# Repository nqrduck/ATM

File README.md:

# ATM (Automatic Tuning and Matching) System

## Automated Tuning and Matching

Tuning and Matching of the resonator coil is an essential part of Nuclear Quadrupole Resonance (NQR) spectroscopy. Because unknown samples are often scanned over large frequency ranges, Tuning and Matching has to be performed frequently. For high Q probe coils using mechanically trimmable capacitors, this is a long and tedious task.
To overcome this issue, an automatic Tuning and Matching system was developed using widely available low-cost components. Stepper drivers control mechanically trimmable capacitors and a microcontroller measures the Return Loss at resonance frequency. The system is capable of Tuning and Matching of a resonator coil in a frequency range from 75 to 125 MHz. It can also measure the Return Loss of the probe coil at its resonance frequency.

Additionally the system is capable of Tuning and Matching of NQR probe coils using varactor diodes. In this case the system can output a Tuning and Matching voltage in a range from 0 to 5V. 

This system is best used in combination with the [NQRduck](https://git.private.coffee/nqrduck) project which provides a graphical user interface for the ATM-system. Specifically, the [nqrduck-autotm](https://git.private.coffee/nqrduck/nqrduck-autotm) module is used to control the ATM-system.

The C++ program is then running on the ESP32 microcontroller. The NQRduck autotm module communicates with the ESP32 microcontroller using the USB interface.

## Features
- Homing of the probe coil steppers using the sensorless load detection of TMC2130 stepper drivers. 
- A mechanically tunable probe coil can be tuned and matched in the frequency range of 75-125MHz.
- $S_{11}$ measurements can be performed at a frequency with a fixed position for the tuning and matching capacitors.
- Electrically tunable probe coils can be tuned and matched in the frequency range of 75-125MHz. 

## System overview
The ATM-system consists of multiple separate hardware components and multiple signal paths. One signal path is used to measure the reflection (characterized by the Return Loss) at a frequency with a fixed position for the tuning and matching capacitors. It is structured as following:

1.  A frequency synthesizer (ADF4351) outputs an RF signal to a filterbank. 
2. The filterbank filters out harmonic components of the frequency synthesizer's output.
3. The filtered signal is guided to a directional coupler setup. The directional coupler is connected to the resonator circuit and decouples the forward signal and the signal reflected at the resonator circuit. 
4. The forward and reflected signals are converted to a DC signal us an AD8302.
5. An ADC reads in the output of the AD8302 and calculates the Return Loss.

Since the system also needs to be able to adjust the mechanically trimmable capacitors, stepper motors have to be controlled.

1. A microcontroller sends commands to two stepper drivers using a Serial Peripheral Interface (SPI).
2. Those stepper drivers control the steppers which are mechanically coupled to the the tuning and matching capacitors of the probe coil.  

For electrically tunable probe coils the ESP32 uses the ADAC click to output a voltage to the varactor diodes.

## Hardware
Schematics for the electrical circuit and mechanical housing will be added soon. 

## Install instructions
1. Download the project as a zip file and import it as a platformio project. 
2. Connect your ESP32 microcontroller to your PC and flash the firmware onto it. 

For the installation of the NQRduck autoTM module please refer to the [NQRduck](https://git.private.coffee/nqrduck) documentation.

# Commands
The user can input different commands to the ATM-system using the serial interface of the ESP32. The general structure of such a command is a single character followed by a float value. The float value is only needed for certain commands.

# Results
A mechanically tunable probe coil was tuned and from 83MHz to 87MHz with a step size of 0.1MHz. The resulting reflection coefficient was then measured using the VNA (ZVL3, Rohde & Schwarz, Munich, Germany). The measured values were plotted using Matplotlib.

For the electrically tunable probe coil the probe coil was tuned and matched from 83 to 84MHz with a step size of 0.1MHz. The resulting reflection coefficient was then measured using the VNA (ZVL3, Rohde & Schwarz, Munich, Germany). The measured values were plotted using Matplotlib.

## Future work
- Optimization for $S_{11}$ measurements. Right now the maximum achievable matching is about -25dB.
- Improve the calibration for $S_{11}$ measurements. Right now the setup is very impractical. 

## References
- [adf4351](https://github.com/dfannin/adf4351) by David Fannin was modified to be used with an ESP32 microcontroller. 
- [TMC2130Stepper](https://github.com/teemuatlut/TMC2130Stepper) by teemuatlut was used for the TMC2130 Stepper drivers.
- [AD5593R](https://github.com/LukasJanavicius/AD5593R-Arduino-ESP32-Library) by LukasJanavicius was used for the AD5593R ADC.
- [ArduiTaM](https://doi.org/10.5194/mr-1-105-2020) by Jouda et al. was an inspiration for the implementation.

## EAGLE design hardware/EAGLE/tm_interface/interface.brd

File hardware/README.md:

# Notes
These files are out of date and are not used in the current version of the ATM. I will update this documentation soon (hopefully).

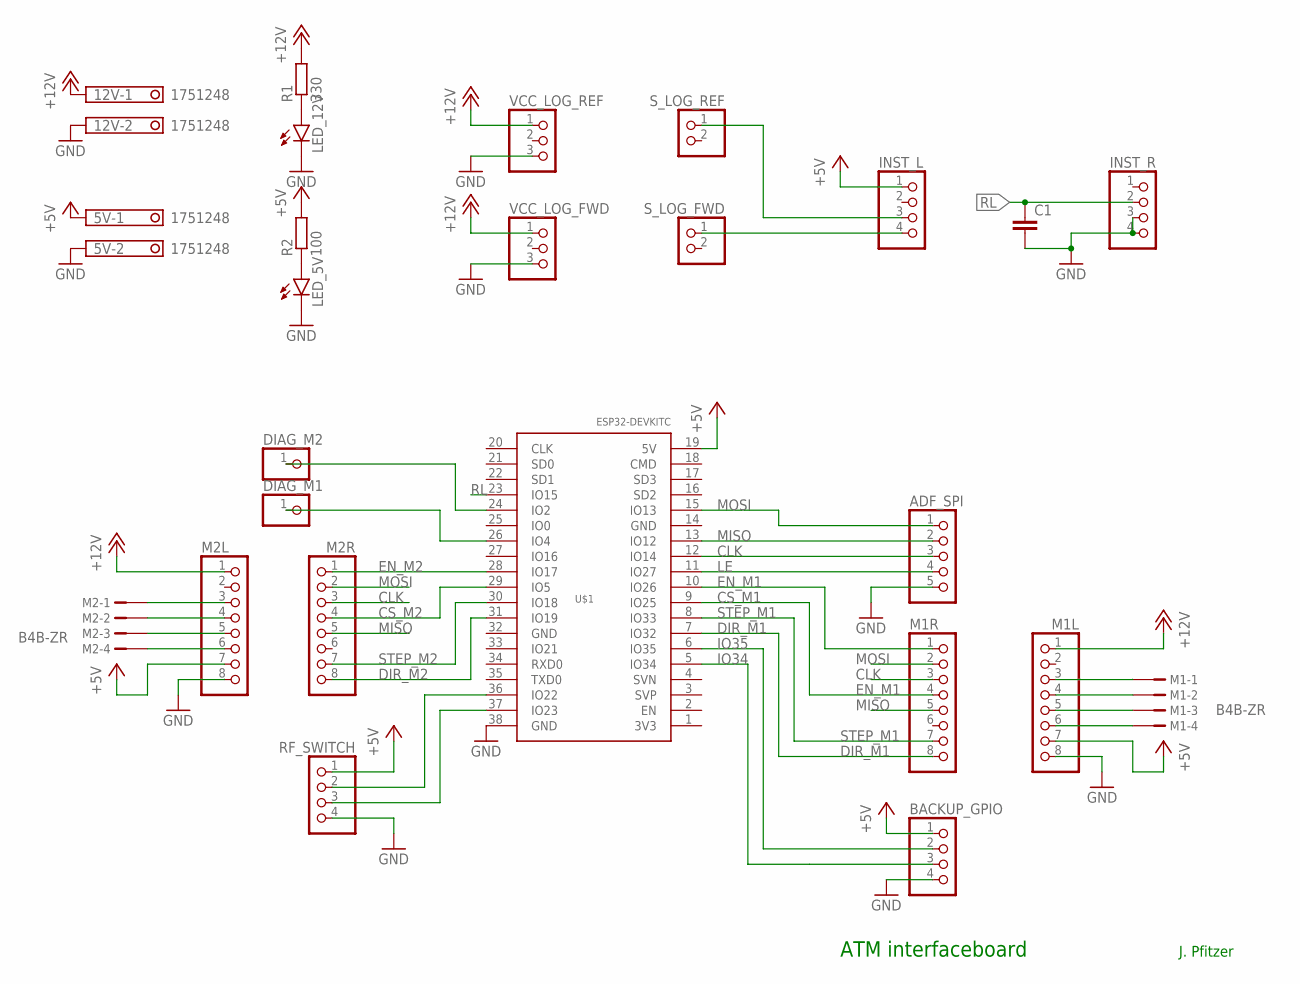
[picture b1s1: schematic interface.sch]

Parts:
5V, 12V: 1751248
ADF_SPI: PINHD-1X5; 1X05
BACKUP_GPIO: PINHD-1X4; 1X04
C1: C-EU025-025X050; C025-025X050
DIAG_M1, DIAG_M2: PINHD-1X1; 1X01
INST_L: PINHD-1X4; 1X04
INST_R: PINHD-1X4; 1X04
LED_5V, LED_12V: LED5MM
M1, M2: B4B-ZR
M1L, M1R, M2L, M2R: PINHD-1X8; 1X08
R1: 330; 0207/12
R2: 100; 0207/12
RF_SWITCH: PINHD-1X4; 1X04
S_LOG_FWD: PINHD-1X2; 1X02
S_LOG_REF: PINHD-1X2; 1X02
U$1: ESP32DEVKITC; ESP32-DEVKITC
VCC_LOG_FWD: PINHD-1X3; 1X03
VCC_LOG_REF: PINHD-1X3; 1X03

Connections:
+5V: 5V.1, BACKUP_GPIO.1, INST_L.1, M1L.7, M2L.7, R2.2, RF_SWITCH.1, U$1.19 (5V)
+12V: 12V.1, M1L.1, M2L.1, R1.2, VCC_LOG_FWD.1, VCC_LOG_REF.1
CLK: ADF_SPI.3, M1R.3, M2R.3, U$1.12 (IO14)
CS_M1: M1R.4, U$1.9 (IO25)
CS_M2: M2R.4, U$1.29 (IO5)
DIR_M1: M1R.8, U$1.7 (IO32)
DIR_M2: M2R.8, U$1.31 (IO19)
EN_M1: M1R.1, U$1.10 (IO26)
EN_M2: M2R.1, U$1.28 (IO17)
GND: 5V.2, 12V.2, ADF_SPI.5, BACKUP_GPIO.4, C1.2, INST_R.3, INST_R.4, LED_5V.K (C), LED_12V.K (C), M1L.8, M2L.8, RF_SWITCH.4, U$1.38 (GND), VCC_LOG_FWD.3, VCC_LOG_REF.3
IO34: BACKUP_GPIO.3, U$1.5 (IO34)
IO35: BACKUP_GPIO.2, U$1.6 (IO35)
LE: ADF_SPI.4, U$1.11 (IO27)
MISO: ADF_SPI.2, M1R.5, M2R.5, U$1.13 (IO12)
MOSI: ADF_SPI.1, M1R.2, M2R.2, U$1.15 (IO13)
unnamed: M1.1, M1L.3
unnamed: M1.2, M1L.4
unnamed: M1.3, M1L.5
unnamed: M1.4, M1L.6
unnamed: M2.1, M2L.3
unnamed: M2.2, M2L.4
unnamed: M2.3, M2L.5
unnamed: M2.4, M2L.6
unnamed: DIAG_M1.1, U$1.26 (IO4)
unnamed: DIAG_M2.1, U$1.24 (IO2)
unnamed: INST_L.3, S_LOG_REF.1
unnamed: INST_L.4, S_LOG_FWD.1
unnamed: RF_SWITCH.2, U$1.36 (IO22)
unnamed: RF_SWITCH.3, U$1.37 (IO23)
unnamed: LED_12V.A, R1.1
unnamed: LED_5V.A, R2.1
RL: C1.1, INST_R.2, U$1.23 (IO15)
STEP_M1: M1R.7, U$1.8 (IO33)
STEP_M2: M2R.7, U$1.30 (IO18)

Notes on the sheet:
ATM interfaceboard
J. Pfitzer

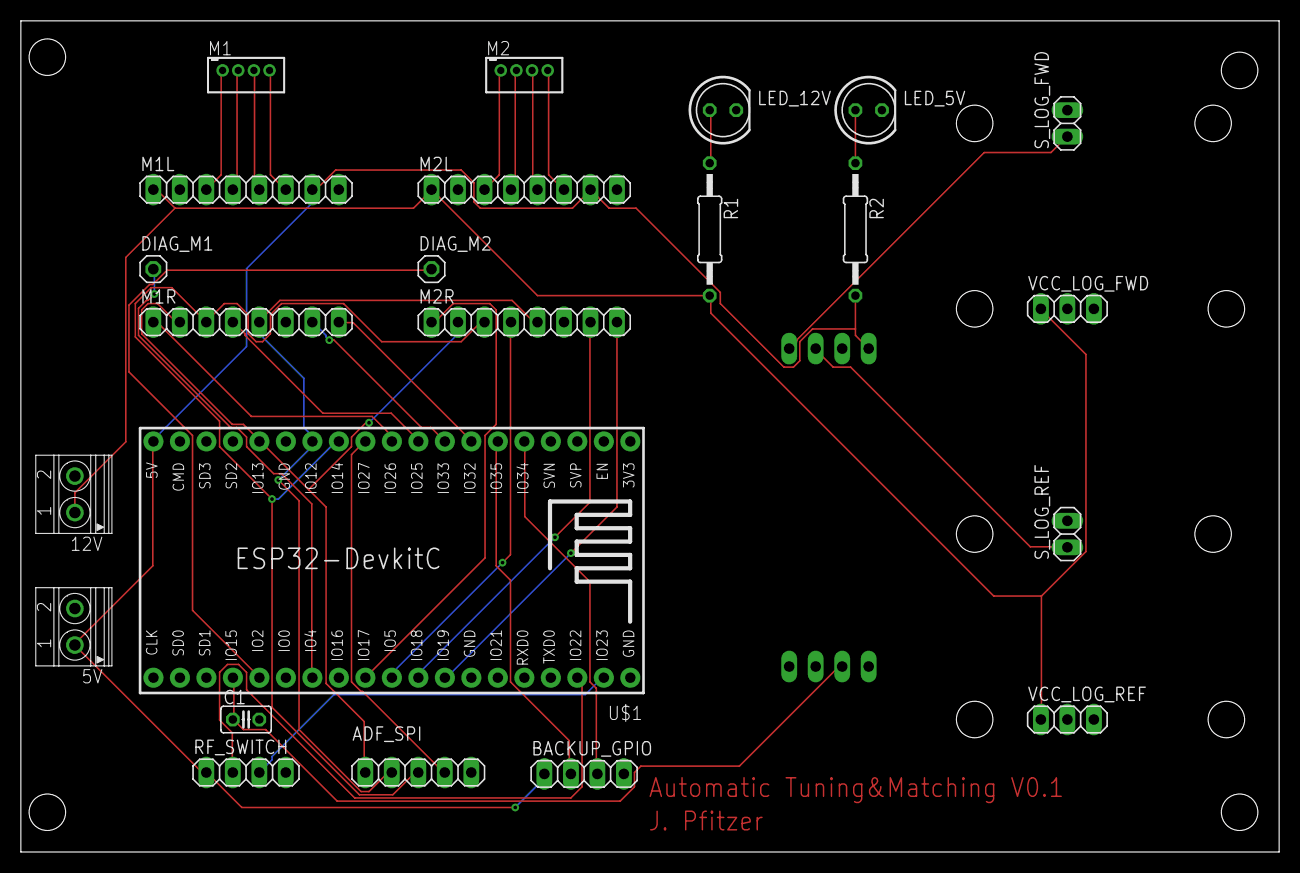
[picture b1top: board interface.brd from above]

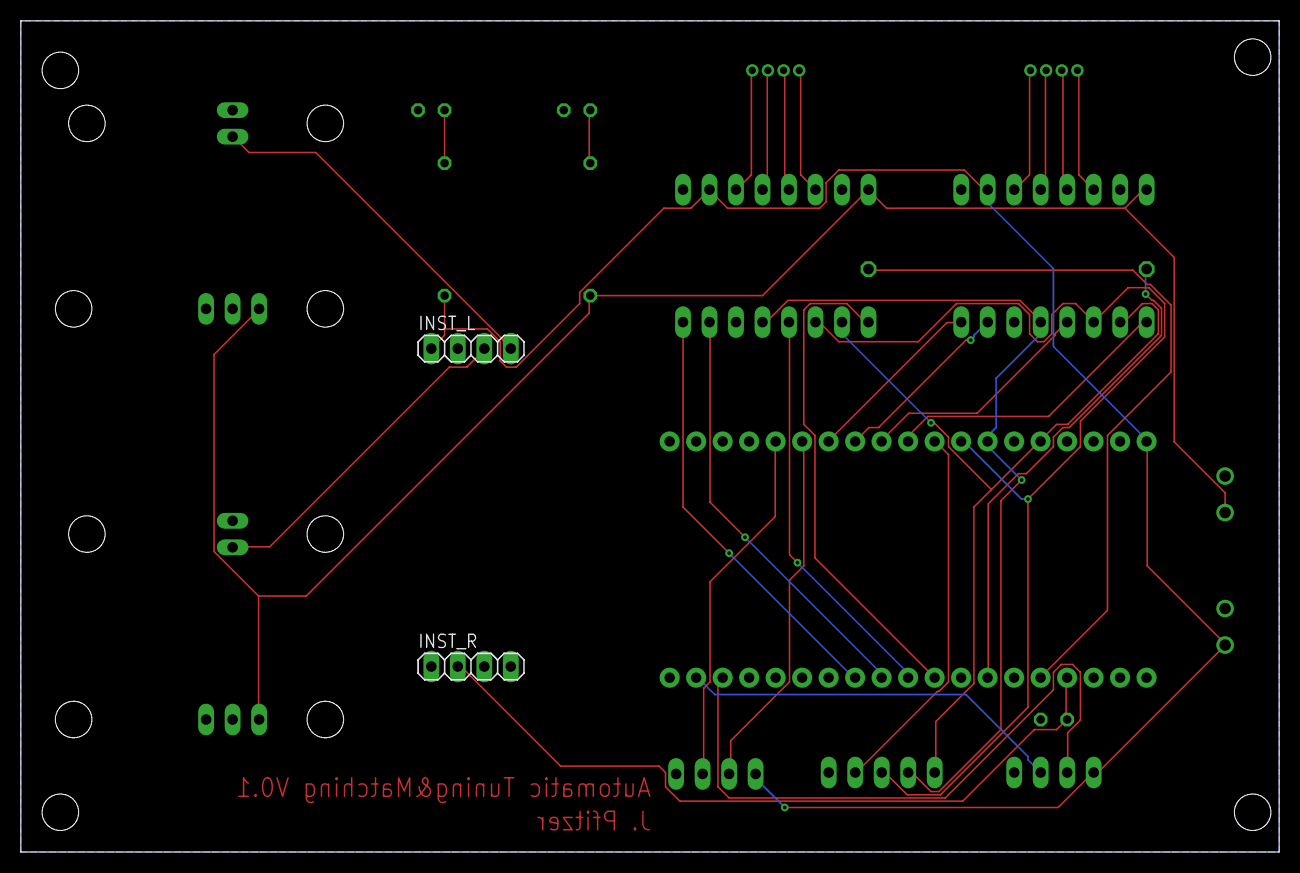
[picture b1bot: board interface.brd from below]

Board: 2 copper layers, 120.6 x 79.7 mm, 25 parts (2 on the bottom side), 34 nets.

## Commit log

2021-12-29 Added general comments.
2021-12-30 Implemented Serial control.
2021-12-30 Implemented rudimentary estimation of Reflection Loss
2022-01-03 Changed units to mV in calculation of RL.
2022-01-03 Added plausibility check to aproximation.
2022-01-03 Implemented homing routine for tuner and matcher.
2022-01-03 Started matching routine.
2022-01-04 Fixed aproximation.
2022-01-04 Fixed another bug in approximation.
2022-01-04 Improved basic matching.
2022-01-04 Implemented sum approach for matching algorithm.
2022-01-04 Added direction choosing for matching.
2022-01-04 Improved matching by adjusting multiple parameters.
2022-01-05 Cleaned up project structure.
2022-01-05 Improved homing routine.
2022-01-05 Started implementation of calibration routine.
2022-01-06 Change to PlatformIO
2022-01-06 Changed Stepper definitions.
2022-01-17 Changed to dual logamp setup.
2022-01-28 Changed back to PlatformIO
2022-01-28 Implemented re-matching if a certain threshold is reached.
2022-01-28 Final commit - formatting.
2022-02-08 Changed power level for improved matching.
2022-02-08 Fixed bug in getMatchRotation function.
2022-02-09 Implemented rematching while brutefrocing resonance
2022-02-09 Implemented capacitor loading for improved resonance search
2022-02-09 Readded sum around resonance for matching algorithm
2022-02-10 Implemented frequency-ranges with filterbank.
2022-02-10 Fixed a bug with homing routine after frequency range change.
2022-02-10 Bugfixes regarding Matching, added improved home-matching points.
2022-02-14 Changed filter selection to default frequency range.
2022-02-17 Updated pins for interface-board.
2022-02-18 Updated to new Hardware.
2022-02-21 Major improvement to matching. Changed Filterbank pins.
2022-02-21 Small adjustments.
2022-03-12 Create LICENSE
2022-03-13 Create CAD
2022-03-13 Added hardware files
2022-03-13 removed identifier file
2022-03-13 added description again, removed comments
2022-03-13 re-added comments
2022-04-05 Added documentation images.
2023-08-07 Changed to new ADC.
2023-08-08 Update to AD8302
2023-08-10 Added RF switch.
2023-08-10 Implemented frequency sweep range.
2023-08-10 Implemented new command structure.
2023-08-10 Updated references.
2023-08-11 Implemented SetVoltages command
2023-08-11 Added docs.
2023-08-11 Updated confirmation message.
2023-08-16 Implemented MeasureReflection command.
2023-08-16 Implemented basic voltage sweep.
2023-08-16 Changed averages and search stop condition.
2023-08-17 Improved voltage sweep.
2023-08-18 Updated RF switch PIN.
2023-08-18 Implemented ControlSwitch command.
2023-08-18 Changed range to new values.
2023-08-18 Added argument for printing of data.
2023-08-18 Improved switching of filters.
2023-08-18 Added frequency sweep method.
2023-08-18 Speed optimization for frequency sweep.
2023-08-21 Added confirmation of commands.
2023-08-21 Improved speed of frequency sweep.
2023-08-22 Implemented MoveStepper command.
2023-08-25 Update setFrequency method for all calls where the frequency has to be set.
2023-12-07 Fixed bug which lead to negative voltages.
2023-12-07 Updated homing.
2023-12-08 Added position update to stepper movement.
2023-12-10 Improved stepper stalling
2023-12-11 Corrected identifier.
2023-12-12 Implemented Backlash Correction and Position Sweep.
2023-12-15 Implemented preset voltage sweep and returning of set voltages for tuning and matching.
2023-12-15 Added feedback on switch state.
2023-12-15 Changed format of commands.
2023-12-15 Removed pritning of voltages text.
2023-12-16 Fixed mixing up of tuning and matching voltages ...
2023-12-20 Updated voltage sweep.
2024-02-21 Updated docs to reflect the current implementation.
2024-02-21 Added results to readme.
2024-02-21 Added note to hardware files.
2025-05-01 Change to forgejo.
